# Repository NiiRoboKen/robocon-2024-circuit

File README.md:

# robocon-2024-circuit
2024年ロボコン関連回路置き場
## esp_md3_servo3_sencor3
### 使用PIN
|機能|PIN|
|--|--|
|dir1|IO21|
|pwm1|IO26|
|dir2|IO22|
|pwm2|IO27|
|dir3|IO23|
|pwm3|IO13|
|servo1|IO4|
|servo2|IO18|
|servo3|IO19|
|sensor1|IO32|
|sensor2|IO33|
|senser3|IO25|

## nucleo_can_md2_roricon2
### 使用PIN
|機能|PIN|
|--|--|
|canRx|PA11|
|canTx|PA12|
|dir1|PA3|
|pwm1|PA4|
|dir2|PA5|
|pwm2|PA6|
|En_A1|PA8|
|En_B1|PA9|
|En_X1|PB0|
|En_A2|PA0|
|En_B2|PA1|
|En_X2|PB1|

## servo_suplly
サーボモーター電源用回路
### 機能
AZ1117-ADJを使ってサーボモータにバッテリーから8Vを降圧し取り出す

## led_supply
LED用電源回路
### 機能
<<<<<<< HEAD
=======
=======
<<<<<<< HEAD
<<<<<<< HEAD
### 機能
=======
###
>>>>>>> bb6cca909106ec396d4f20f676fbe40207585f12
>>>>>>> 1ea0d17096d1d973bdc5ca4e6b00e90c575babdf
=======
###
>>>>>>> bb6cca909106ec396d4f20f676fbe40207585f12
>>>>>>> 1ea0d17096d1d973bdc5ca4e6b00e90c575babdf
>>>>>>> 1733059777e18da8b1199c57d2cf031a569b02b5
22.2Vを12Vに降圧

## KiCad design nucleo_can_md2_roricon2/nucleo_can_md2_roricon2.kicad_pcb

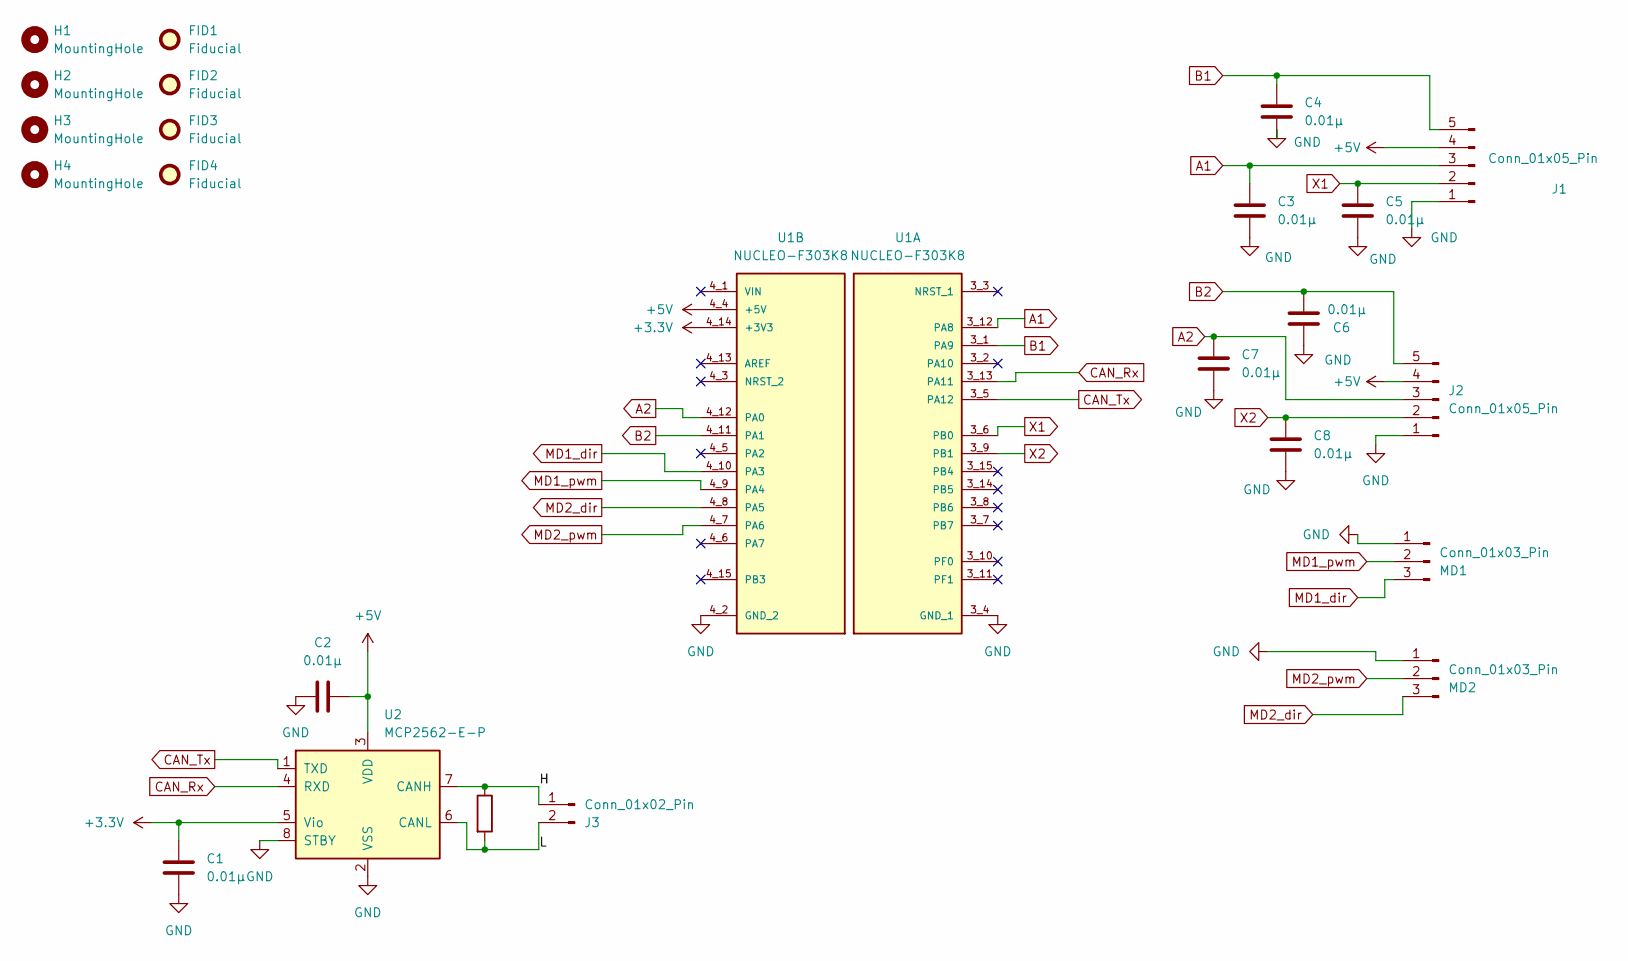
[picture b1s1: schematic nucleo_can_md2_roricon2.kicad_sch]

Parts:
C1, C2, C3, C4, C5, C6, C7, C8: 0.01μ; C_Disc_D4.3mm_W1.9mm_P5.00mm
FID1, FID2, FID3, FID4: Fiducial; Fiducial_0.5mm_Mask1.5mm
H1, H2, H3, H4: MountingHole; MountingHole_2.1mm
J1, J2: Conn_01x05_Pin; JST_XA_S05B-XASK-1N-BN_1x05_P2.50mm_Horizontal
J3: Conn_01x02_Pin; JST_XH_B2B-XH-A_1x02_P2.50mm_Vertical
MD1, MD2: Conn_01x03_Pin; JST_XA_S03B-XASK-1N-BN_1x03_P2.50mm_Horizontal
R1: 120; R_Axial_DIN0207_L6.3mm_D2.5mm_P2.54mm_Vertical
U1: NUCLEO-F303K8; MODULE_NUCLEO-F303K8; PARTREV 5
U2: MCP2562-E-P; DIP-8_W7.62mm

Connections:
+3.3V: C1.2, U1.4_14 (+3V3), U2.5 (Vio)
+5V: C2.2, J1.4, J2.4, U1.4_4 (+5V), U2.3 (VDD)
/H: J3.1, R1.1, U2.7 (CANH)
/L: J3.2, R1.2, U2.6 (CANL)
A1: C3.1, J1.3, U1.3_12 (PA8)
A2: C7.1, J2.3, U1.4_12 (PA0)
B1: C4.1, J1.5, U1.3_1 (PA9)
B2: C6.2, J2.5, U1.4_11 (PA1)
CAN_Rx: U1.3_13 (PA11), U2.4 (RXD)
CAN_Tx: U1.3_5 (PA12), U2.1 (TXD)
GND: C1.1, C2.1, C3.2, C4.2, C5.2, C6.1, C7.2, C8.2, J1.1, J2.1, MD1.1, MD2.1, U1.3_4 (GND_1), U1.4_2 (GND_2), U2.2 (VSS), U2.8 (STBY)
MD1_dir: MD1.3, U1.4_10 (PA3)
MD1_pwm: MD1.2, U1.4_9 (PA4)
MD2_dir: MD2.3, U1.4_8 (PA5)
MD2_pwm: MD2.2, U1.4_7 (PA6)
X1: C5.1, J1.2, U1.3_6 (PB0)
X2: C8.1, J2.2, U1.3_9 (PB1)

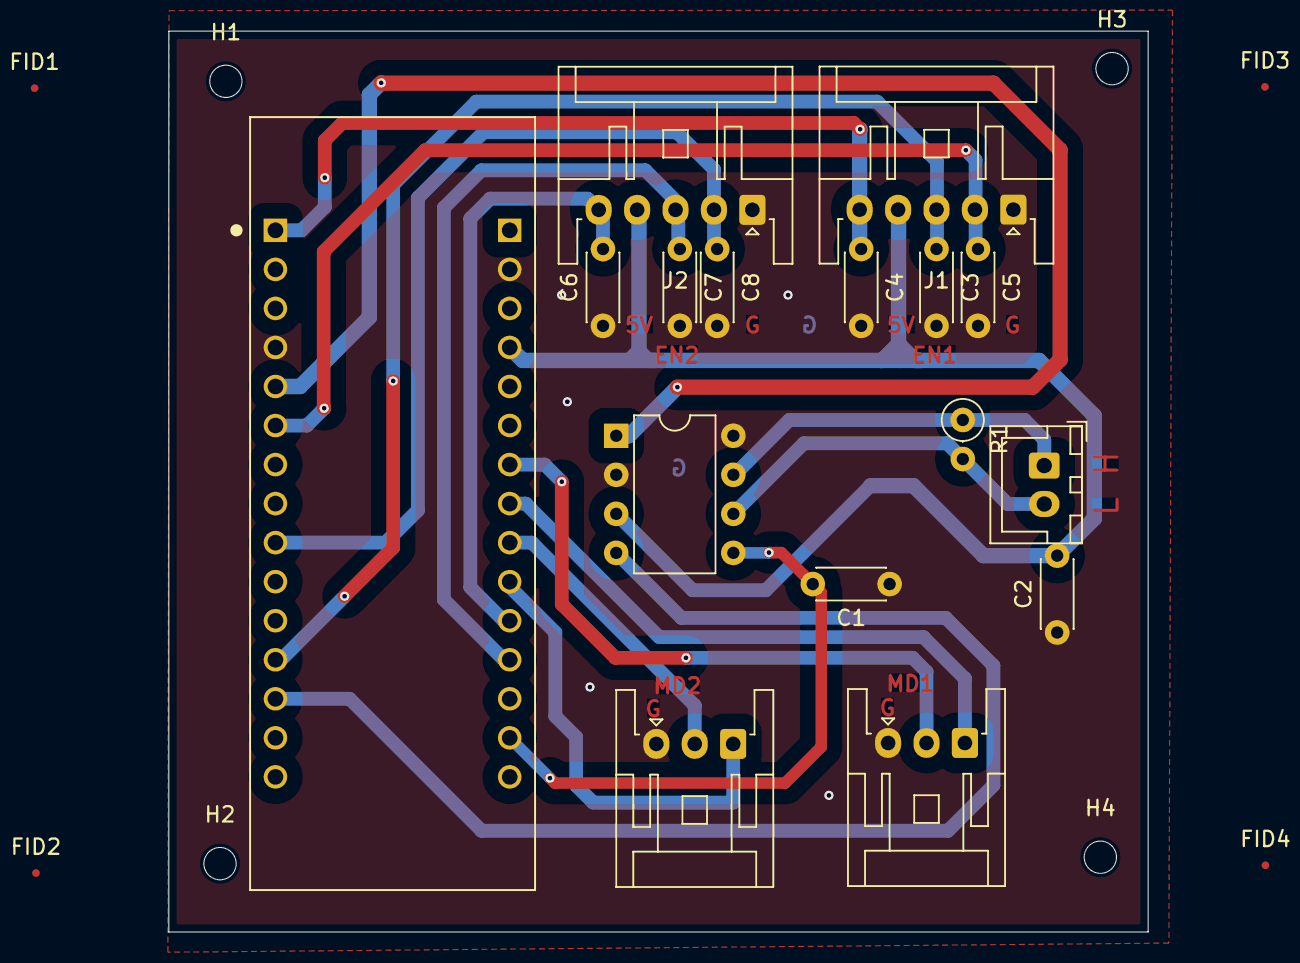
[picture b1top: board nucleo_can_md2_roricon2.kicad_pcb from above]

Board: 2 copper layers, 63.7 x 58.6 mm, 24 parts (0 on the bottom side), 17 nets.

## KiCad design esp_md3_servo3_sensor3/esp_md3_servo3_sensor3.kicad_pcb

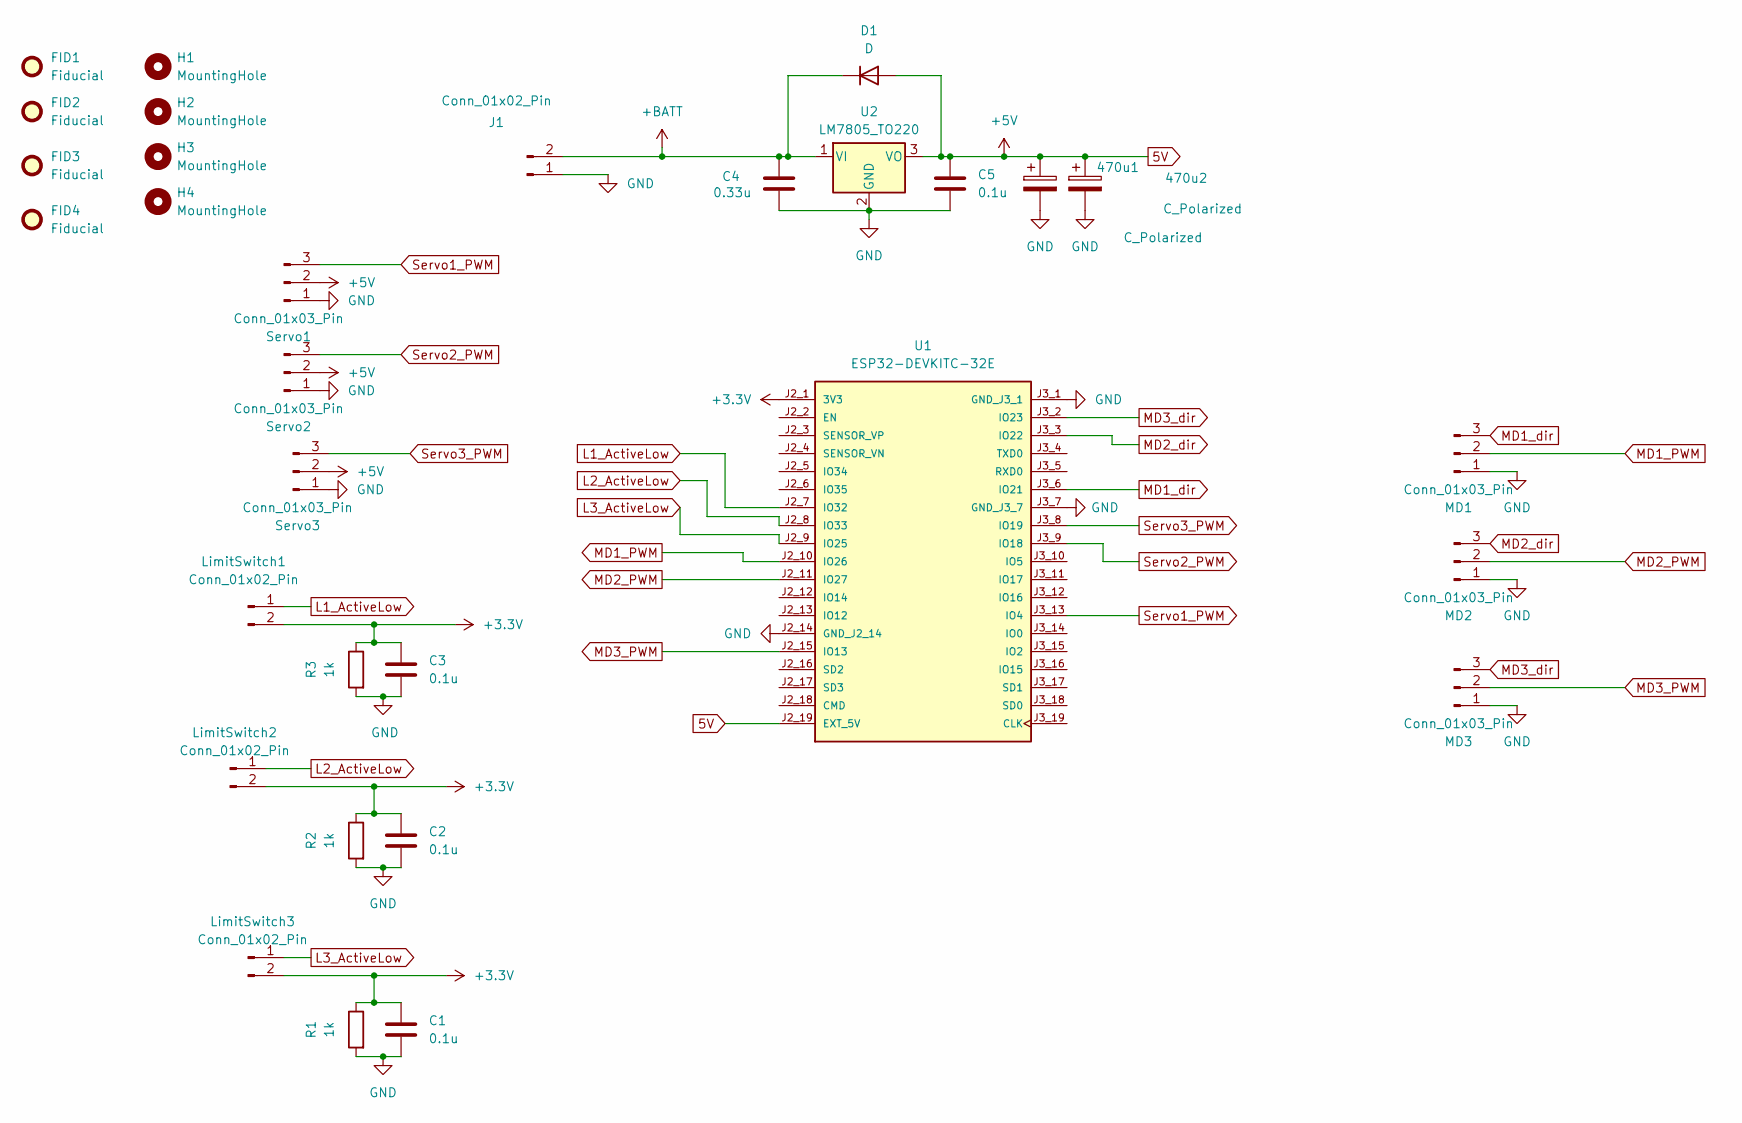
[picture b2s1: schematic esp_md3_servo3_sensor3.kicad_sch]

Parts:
470u1, 470u2: C_Polarized; CP_Radial_Tantal_D8.0mm_P2.50mm
C1, C2, C3, C5: 0.1u; C_Disc_D3.4mm_W2.1mm_P2.50mm
C4: 0.33u; C_Disc_D3.4mm_W2.1mm_P2.50mm
D1: D; D_A-405_P7.62mm_Horizontal
FID1, FID2, FID3, FID4: Fiducial; Fiducial_0.5mm_Mask1.5mm
H1, H2, H3, H4: MountingHole; MountingHole_2.1mm
J1: Conn_01x02_Pin; AMASS_XT30U-F_1x02_P5.0mm_Vertical
LimitSwitch1, LimitSwitch2, LimitSwitch3: Conn_01x02_Pin; JST_XH_B2B-XH-A_1x02_P2.50mm_Vertical
MD1, MD2, MD3: Conn_01x03_Pin; JST_XH_S3B-XH-A-1_1x03_P2.50mm_Horizontal
R1, R2, R3: 1k; R_Axial_DIN0207_L6.3mm_D2.5mm_P10.16mm_Horizontal
Servo1, Servo2, Servo3: Conn_01x03_Pin; JST_XH_S3B-XH-A-1_1x03_P2.50mm_Horizontal
U1: ESP32-DEVKITC-32E; MODULE_ESP32-DEVKITC-32E; PARTREV 1.4
U2: LM7805_TO220; TO-220F-3_Horizontal_TabDownananasi

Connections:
5V: 470u1.1, 470u2.1, C5.1, D1.2 (A), Servo1.2, Servo2.2, Servo3.2, U1.J2_19 (EXT_5V), U2.3 (VO)
+3.3V: C1.1, C2.1, C3.1, LimitSwitch1.2, LimitSwitch2.2, LimitSwitch3.2, R1.1, R2.1, R3.1, U1.J2_1 (3V3)
+BATT: C4.1, D1.1 (K), J1.2, U2.1 (VI)
GND: 470u1.2, 470u2.2, C1.2, C2.2, C3.2, C4.2, C5.2, J1.1, MD1.1, MD2.1, MD3.1, R1.2, R2.2, R3.2, Servo1.1, Servo2.1, Servo3.1, U1.J2_14 (GND_J2_14), U1.J3_1 (GND_J3_1), U1.J3_7 (GND_J3_7), U2.2 (GND)
L1_ActiveLow: LimitSwitch1.1, U1.J2_7 (IO32)
L2_ActiveLow: LimitSwitch2.1, U1.J2_8 (IO33)
L3_ActiveLow: LimitSwitch3.1, U1.J2_9 (IO25)
MD1_PWM: MD1.2, U1.J2_10 (IO26)
MD1_dir: MD1.3, U1.J3_6 (IO21)
MD2_PWM: MD2.2, U1.J2_11 (IO27)
MD2_dir: MD2.3, U1.J3_3 (IO22)
MD3_PWM: MD3.2, U1.J2_15 (IO13)
MD3_dir: MD3.3, U1.J3_2 (IO23)
Servo1_PWM: Servo1.3, U1.J3_13 (IO4)
Servo2_PWM: Servo2.3, U1.J3_9 (IO18)
Servo3_PWM: Servo3.3, U1.J3_8 (IO19)

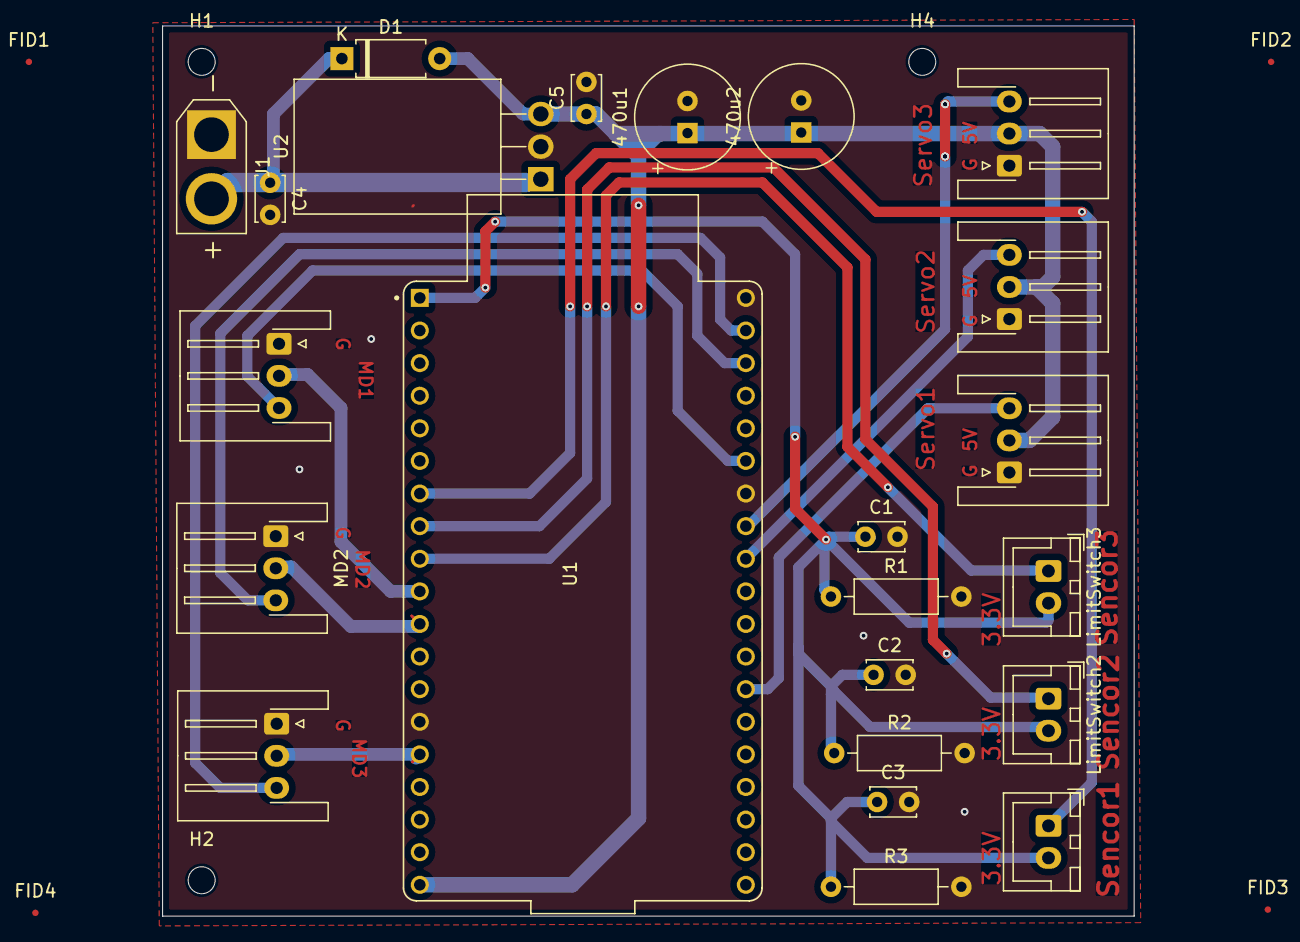
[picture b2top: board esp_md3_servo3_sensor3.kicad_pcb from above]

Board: 2 copper layers, 75.7 x 69.3 mm, 30 parts (0 on the bottom side), 16 nets.

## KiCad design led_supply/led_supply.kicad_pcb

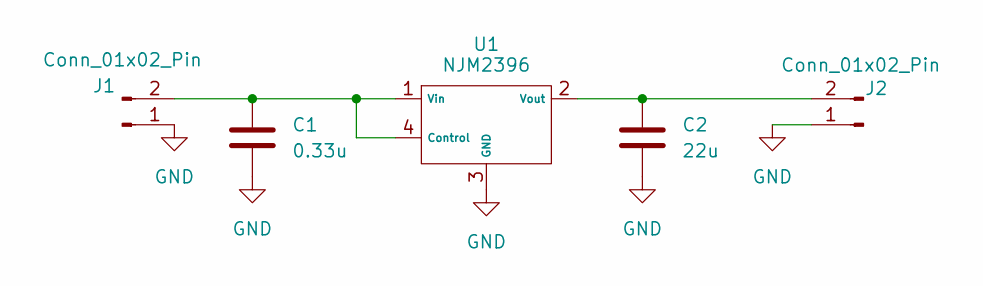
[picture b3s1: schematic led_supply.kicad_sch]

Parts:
C1: 0.33u; C_Disc_D5.0mm_W2.5mm_P5.00mm
C2: 22u; C_Disc_D5.0mm_W2.5mm_P5.00mm
J1: Conn_01x02_Pin; AMASS_XT30U-F_1x02_P5.0mm_Vertical
J2: Conn_01x02_Pin; AMASS_XT30U-M_1x02_P5.0mm_Vertical
U1: NJM2396

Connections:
GND: C1.2, C2.2, J1.1, J2.1, U1.3 (GND)
unnamed: C1.1, J1.2, U1.1 (Vin), U1.4 (Control)
unnamed: C2.1, J2.2, U1.2 (Vout)

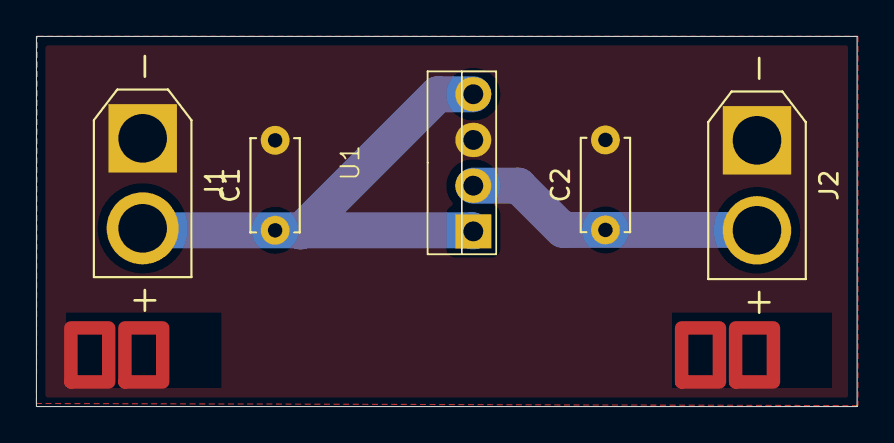
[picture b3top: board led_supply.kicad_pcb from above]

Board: 2 copper layers, 45.6 x 20.6 mm, 5 parts (0 on the bottom side), 3 nets.

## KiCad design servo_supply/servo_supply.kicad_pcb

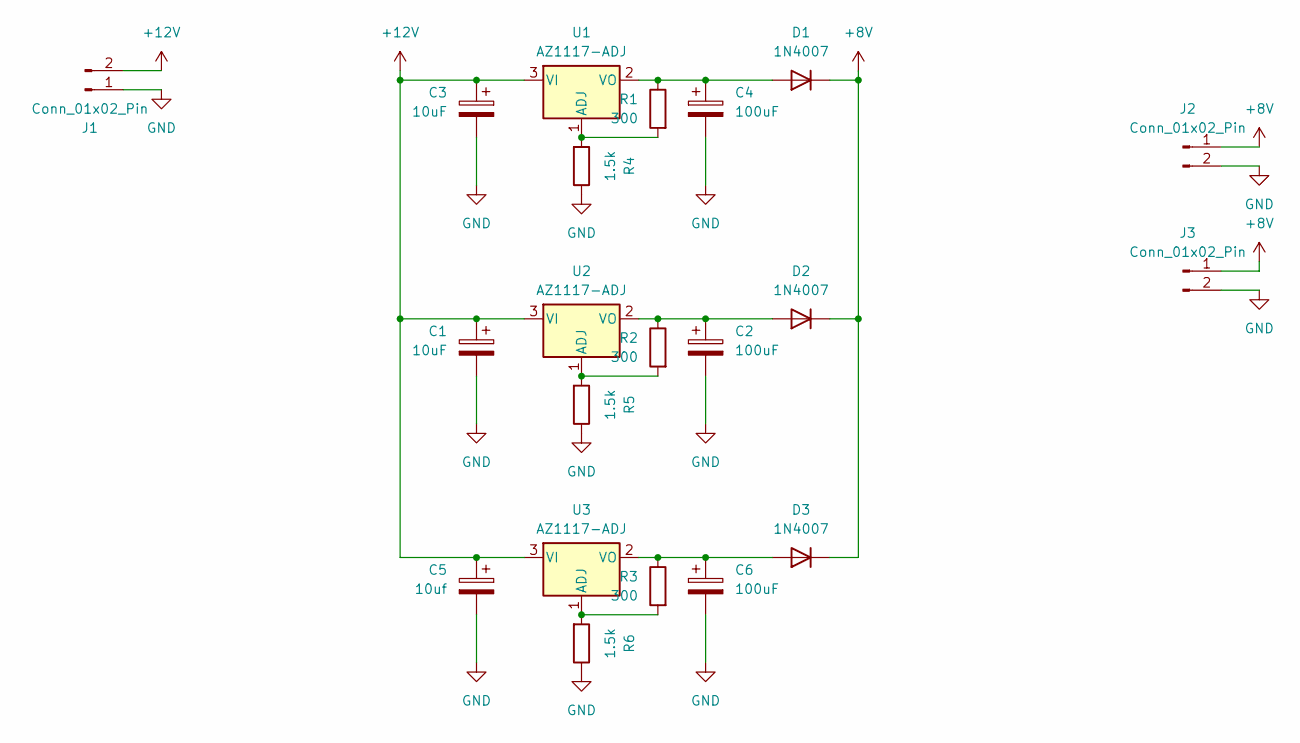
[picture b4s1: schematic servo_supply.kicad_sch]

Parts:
C1, C3: 10uF; CP_Radial_D5.0mm_P2.50mm
C2, C4, C6: 100uF; CP_Radial_D5.0mm_P2.50mm
C5: 10uf; CP_Radial_D5.0mm_P2.50mm
D1, D2, D3: 1N4007; D_DO-41_SOD81_P10.16mm_Horizontal
J1: Conn_01x02_Pin; AMASS_XT30U-M_1x02_P5.0mm_Vertical
J2, J3: Conn_01x02_Pin; JST_EH_B2B-EH-A_1x02_P2.50mm_Vertical
R1, R2, R3: 300; R_Axial_DIN0207_L6.3mm_D2.5mm_P2.54mm_Vertical
R4, R5, R6: 1.5k; R_Axial_DIN0207_L6.3mm_D2.5mm_P2.54mm_Vertical
U1, U2, U3: AZ1117-ADJ; SOT-223-3_TabPin2

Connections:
+8V: D1.1 (K), D2.1 (K), D3.1 (K), J2.1, J3.1
+12V: C1.1, C3.1, C5.1, J1.2, U1.3 (VI), U2.3 (VI), U3.3 (VI)
GND: C1.2, C2.2, C3.2, C4.2, C5.2, C6.2, J1.1, J2.2, J3.2, R4.1, R5.1, R6.1
unnamed: C4.1, D1.2 (A), R1.1, U1.2 (VO)
unnamed: C2.1, D2.2 (A), R2.1, U2.2 (VO)
unnamed: C6.1, D3.2 (A), R3.1, U3.2 (VO)
unnamed: R1.2, R4.2, U1.1 (ADJ)
unnamed: R2.2, R5.2, U2.1 (ADJ)
unnamed: R3.2, R6.2, U3.1 (ADJ)

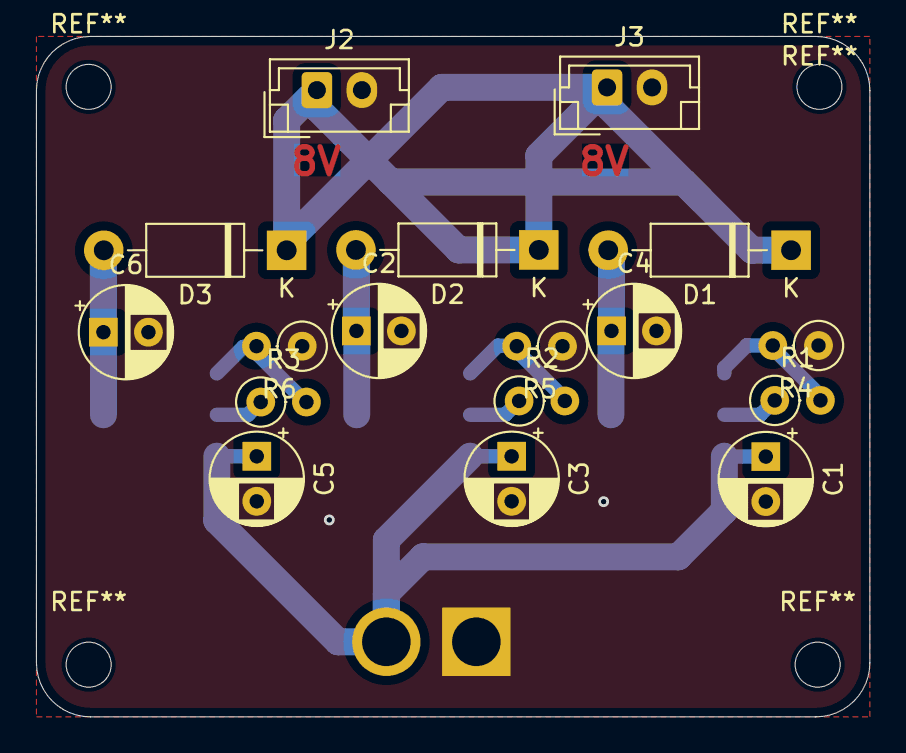
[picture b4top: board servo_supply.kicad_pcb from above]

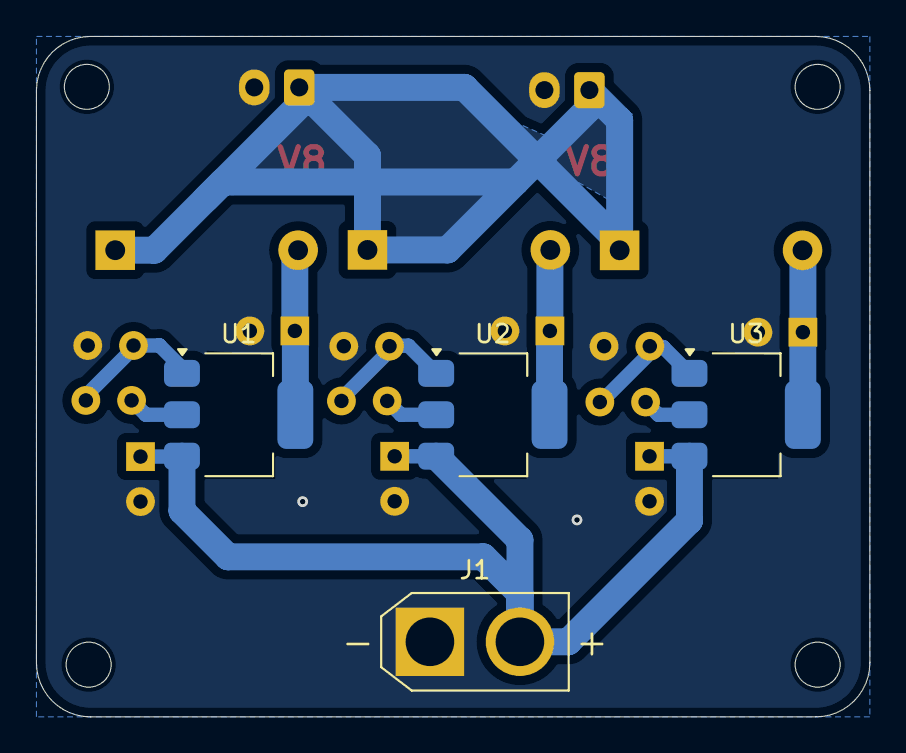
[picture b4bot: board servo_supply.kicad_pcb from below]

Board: 2 copper layers, 46.3 x 37.8 mm, 21 parts (4 on the bottom side), 9 nets.

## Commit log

2024-08-29 .gitiignoreを追加
2024-08-29 feat:first commit
2024-08-30 feat:エンコーダー機能付きSTMを追加
2024-09-01 feat:readmeを編集
2024-09-01 docs: *.lck
2024-09-01 feat:servo_supplyを追加
2024-09-04 feat:接続ミスを修正
2024-09-04 feat:bug修正
2024-09-05 feat:文字位置を修正
2024-09-05 feat:文字を追加
2024-09-19 docs: led_supplyの説明を追加
2024-09-19 ミスを修正
2024-09-19 docs: READMEの追加
2024-09-25 3.3v
